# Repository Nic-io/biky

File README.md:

# biky
blinking bike lights

Made with Freecad Kicad and love.

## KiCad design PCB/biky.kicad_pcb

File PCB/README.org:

#+TITLE: PCB design of biky project

* Contains Latest version

** TODO Make version 2 [1/2]
+ [ ] bigger pin header
+ [X] etc

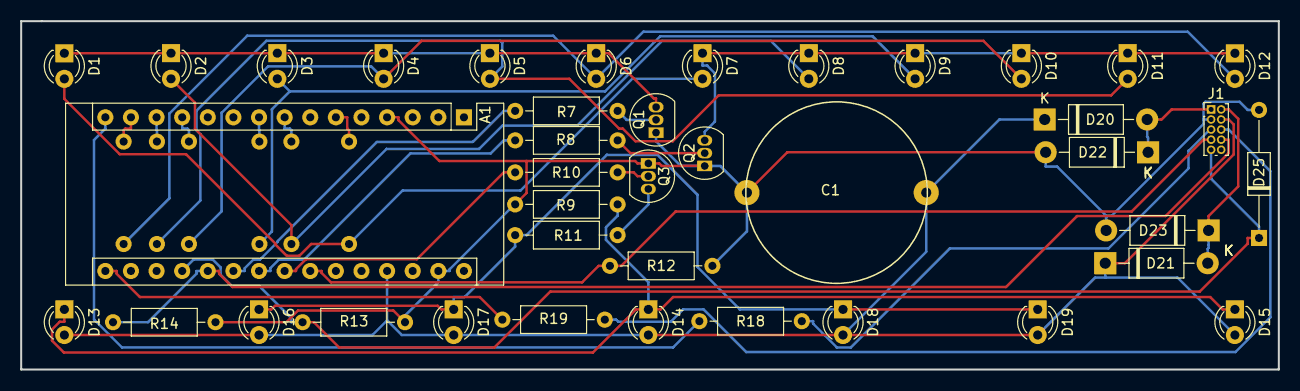
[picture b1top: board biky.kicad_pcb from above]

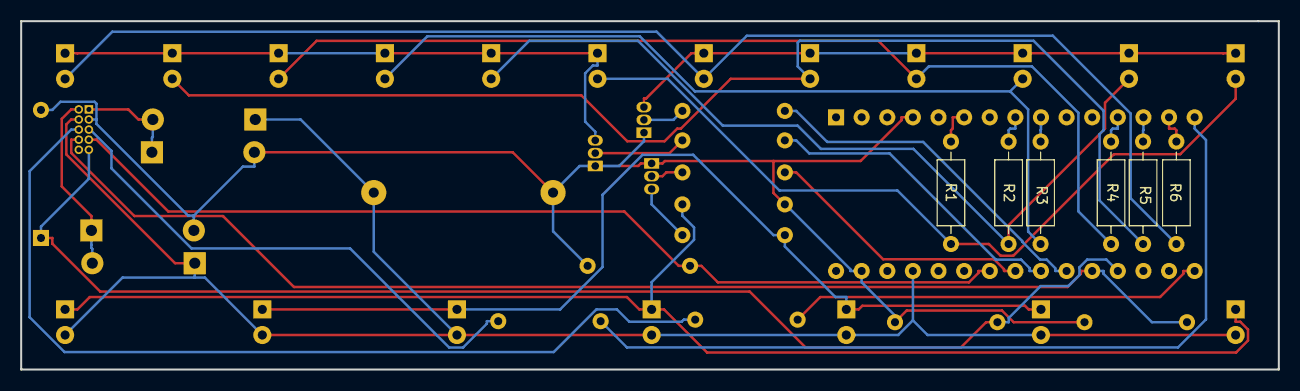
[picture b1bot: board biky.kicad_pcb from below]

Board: 2 copper layers, 124.7 x 34.5 mm, 46 parts (6 on the bottom side), 34 nets.

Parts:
A1: Arduino_Nano_v3.x; Arduino_Nano
C1: 1F; Supercap
D1, D2, D3, D4, D5, D6, D7, D8, D9, D10, D11, D12: yellow; LED_D3.0mm
D13: Red; LED_D3.0mm
D14, D15, D16, D17, D18, D19: red; LED_D3.0mm
D20, D21, D22, D23: 1N4007; D_DO-41_SOD81_P10.16mm_Horizontal
D25: Vz10V; D_DO-35_SOD27_P12.70mm_Horizontal
J1: Conn_02x05_Odd_Even; PinHeader_2x05_P1.00mm_Vertical
Q1, Q2, Q3: PN2222A; TO-92_Inline
R1, R2, R3, R4, R5, R6: 47; R_Axial_DIN0207_L6.3mm_D2.5mm_P10.16mm_Horizontal
R7, R8: 940; R_Axial_DIN0207_L6.3mm_D2.5mm_P10.16mm_Horizontal
R9, R11: 22; R_Axial_DIN0207_L6.3mm_D2.5mm_P10.16mm_Horizontal
R10: 400; R_Axial_DIN0207_L6.3mm_D2.5mm_P10.16mm_Horizontal
R12, R13, R14: 1M; R_Axial_DIN0207_L6.3mm_D2.5mm_P10.16mm_Horizontal
R18, R19: 80; R_Axial_DIN0207_L6.3mm_D2.5mm_P10.16mm_Horizontal

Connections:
+5V: A1.27, C1.1, D13.2, D14.2, D15.2, D16.2, D17.2, D18.2, D19.2, D20.1, D21.1, J1.4
/BrakeON: A1.23, R10.2
/BrakeSense: A1.24, J1.7, R12.2
/Dynamo+: D20.2, D22.1, J1.1
/Dynamo-: D21.2, D23.1, J1.2
/Leftswitch: A1.19, D25.1, J1.9, R13.2
/LightButtonLeft: J1.5, R18.2
/LightButtonRigh: J1.6, R19.2
/PWM1: A1.6, R1.2
/PWM2: A1.8, R2.2
/PWM3: A1.9, R3.2
/PWM4: A1.12, R4.2
/PWM5: A1.13, R5.2
/PWM6: A1.14, R6.2
/Rightswitch: A1.20, J1.8, R14.2
/Segment1: A1.21, R7.2
/Segment2: A1.22, R8.2
GND: A1.4, A1.29, C1.2, D22.2, D23.2, D25.2, J1.3, Q1.1, Q2.1, Q3.1, R9.1, R12.1, R13.1, R14.1
unnamed: A1.15, R18.1
unnamed: A1.16, R19.1
unnamed: D1.1, D2.1, D3.1, D4.1, D5.1, D6.1, Q1.3
unnamed: D1.2, D7.2, R1.1
unnamed: D2.2, D8.2, R2.1
unnamed: D3.2, D9.2, R3.1
unnamed: D7.1, D8.1, D9.1, D10.1, D11.1, D12.1, Q2.3
unnamed: D4.2, D10.2, R4.1
unnamed: D5.2, D11.2, R5.1
unnamed: D6.2, D12.2, R6.1
unnamed: D13.1, D14.1, D15.1, R9.2
unnamed: D16.1, D17.1, D18.1, D19.1, R11.2
unnamed: Q1.2, R7.1
unnamed: Q2.2, R8.1
unnamed: Q3.2, R10.1
unnamed: Q3.3, R11.1

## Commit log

2021-11-25 Mark 1 ready+
2021-11-25 add pictures
2021-11-25 add gitignore
2021-12-04 no regulator
2022-02-01 add org page PCB
2022-03-09 corrected connecitons and display
2022-03-09 update case image
2022-03-10 further implementation of ligth control. Uses protothreads, Interrupts and preemption would be nice
2022-03-10 connectors placement
2022-03-10 testing orgfiles as readme
